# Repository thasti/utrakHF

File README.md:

# utrakHF

A pico-balloon tracker implementing WSPR transmission on ham radio frequencies.

## Usage

For launch of this payload, a valid amateur radio callsign and permission for use on an airborne vehicle is required. To configure the software for flight, edit the defines for primary and secondary callsigns in tlm.h. The assignment of secondary callsigns is handled on KD2EAT's web site: http://hojoham.blogspot.com/2016/10/known-flight-ids.html

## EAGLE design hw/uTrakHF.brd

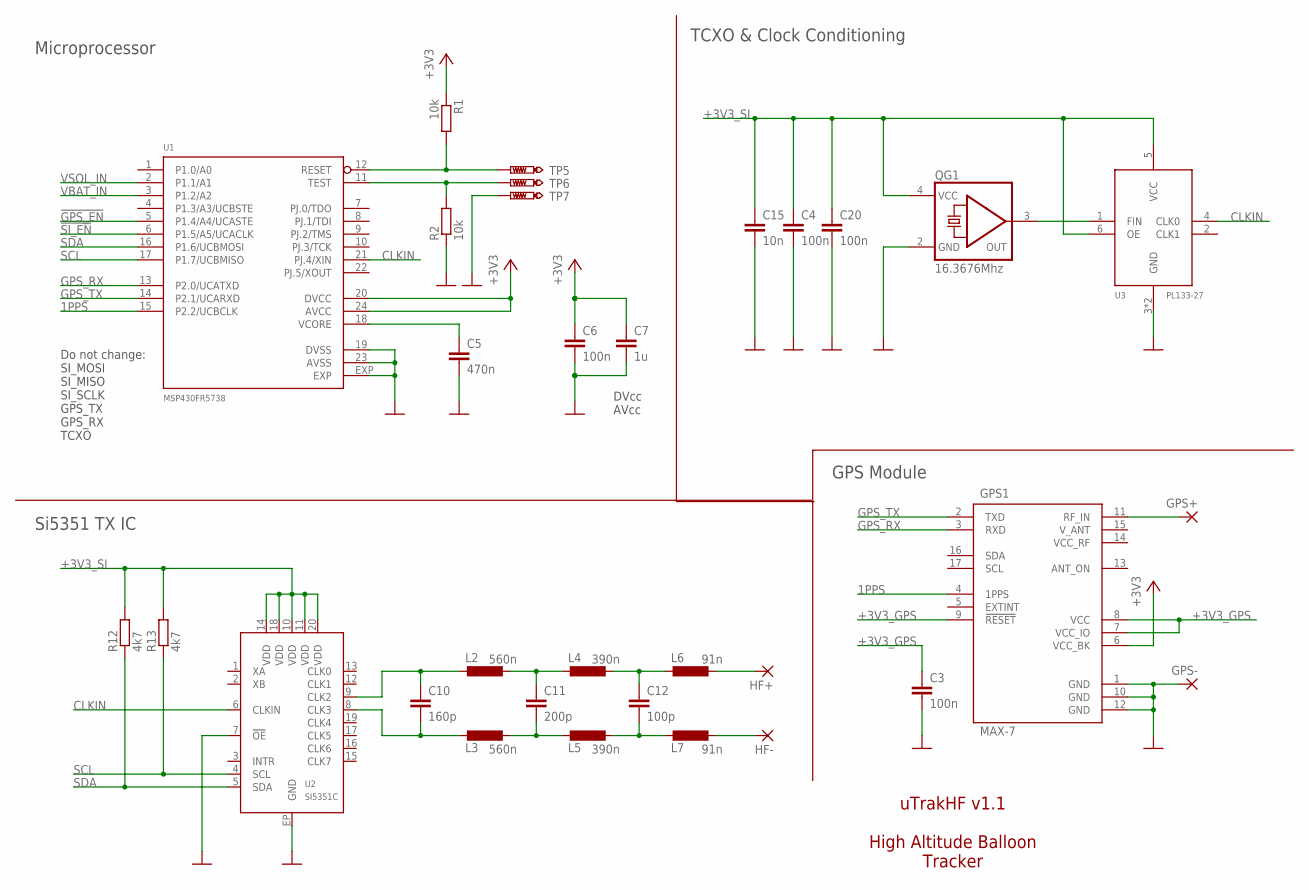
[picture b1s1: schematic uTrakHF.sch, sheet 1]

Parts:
C3, C4, C6, C20: 100n; C0402; PARTNO 81-GRM155R71C104KA88
C5: 470n; C0603; PARTNO 81-GCM188R71C474KA5D
C7: 1u; C0603; PARTNO 81-GRM39R105K10
C10: 160p; C0402; PARTNO 81-GRM1555C1H161JA01
C11: 200p; C0402; PARTNO 81-GRM1555C1H201JA1D
C12: 100p; C0402; PARTNO 81-GRM1555C1H101JA1D
C15: 10n; C0402; PARTNO 81-GRM155R71H103MA8D
GPS1: MAX-7; UBLOX-7
GPS+: SMD2; SMD1,27-2,54
GPS-: SMD2; SMD1,27-2,54
HF+: SMD2; SMD1,27-2,54
HF-: SMD2; SMD1,27-2,54
L2, L3: 560n; C0603; PARTNO 810-MLJ1608WR56JT000
L4, L5: 390n; C0603; PARTNO 810-MLJ1608WR39JT000
L6, L7: 91n; C0603; PARTNO 81-LQW18AN91NG00D
QG1: 16.3676Mhz; CTS406
R1, R2: 10k; R0402; PARTNO 603-RC0402FR-0710KL
R12, R13: 4k7; R0402; PARTNO 603-RC0402FR-074K7L
TP5, TP6, TP7: PTR1TP10SQ; TP10SQ
U1: MSP430FR5738; QFN24-4X4; PARTNO 595-SP430FR5738IRGER
U2: SI5351C; QFN20-4X4; PARTNO 634-SI5351C-B-GM
U3: PL133-27; DFN6-2X3; PARTNO 998-PL133-27GC-R

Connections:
1PPS: GPS1.4 (1PPS), U1.15 (P2.2/UCBCLK)
!GPS_EN: U1.5 (P1.4/A4/UCASTE); also elsewhere on the board
!SI_EN: U1.6 (P1.5/A5/UCACLK); also elsewhere on the board
+3V3: C6.1, C7.1, GPS1.6 (VCC_BK), R1.1, U1.20 (DVCC), U1.24 (AVCC); also elsewhere on the board
+3V3_GPS: C3.1, GPS1.7 (VCC_IO), GPS1.8 (VCC), GPS1.9 (!RESET); also elsewhere on the board
+3V3_SI: C4.1, C15.1, C20.1, QG1.4 (VCC), R12.2, R13.2, U2.10 (VDD), U2.11 (VDD), U2.14 (VDD), U2.18 (VDD), U2.20 (VDD), U3.5 (VCC), U3.6 (OE); also elsewhere on the board
C33: C10.1, L2.1, U2.9 (CLK2)
CLKIN: U1.21 (PJ.4/XIN), U2.6 (CLKIN), U3.4 (CLK0)
GND: C3.2, C4.2, C5.2, C6.2, C7.2, C15.2, C20.2, GPS1.1 (GND), GPS1.10 (GND), GPS1.12 (GND), GPS-.1, QG1.2 (GND), R2.1, TP7.TP, U1.19 (DVSS), U1.23 (AVSS), U1.EXP, U2.7 (!OE), U2.EP (GND), U3.3 (GND), U3.EXP (GND); also elsewhere on the board
GPS+: GPS1.11 (RF_IN), GPS+.1
GPS_RX: GPS1.3 (RXD), U1.13 (P2.0/UCATXD)
GPS_TX: GPS1.2 (TXD), U1.14 (P2.1/UCARXD)
HF+: HF+.1, L6.2
HF-: HF-.1, L7.2
unnamed: C5.1, U1.18 (VCORE)
unnamed: C11.1, L2.2, L4.1
unnamed: C12.1, L4.2, L6.1
unnamed: C10.2, L3.1, U2.8 (CLK3)
unnamed: C11.2, L3.2, L5.1
unnamed: C12.2, L5.2, L7.1
RST: R1.2, TP5.TP, U1.12 (RESET)
SCL: R13.1, U1.17 (P1.7/UCBMISO), U2.4 (SCL)
SDA: R12.1, U1.16 (P1.6/UCBMOSI), U2.5 (SDA)
TCXO: QG1.3 (OUT), U3.1 (FIN)
TST: R2.2, TP6.TP, U1.11 (TEST)
VBAT_IN: U1.3 (P1.2/A2); also elsewhere on the board
VSOL_IN: U1.2 (P1.1/A1); also elsewhere on the board

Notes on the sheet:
GPS Module
Microprocessor
DVcc AVcc
Do not change: SI_MOSI SI_MISO SI_SCLK GPS_TX GPS_RX TCXO
Si5351 TX IC
TCXO & Clock Conditioning
uTrakHF v1.1 High Altitude Balloon Tracker

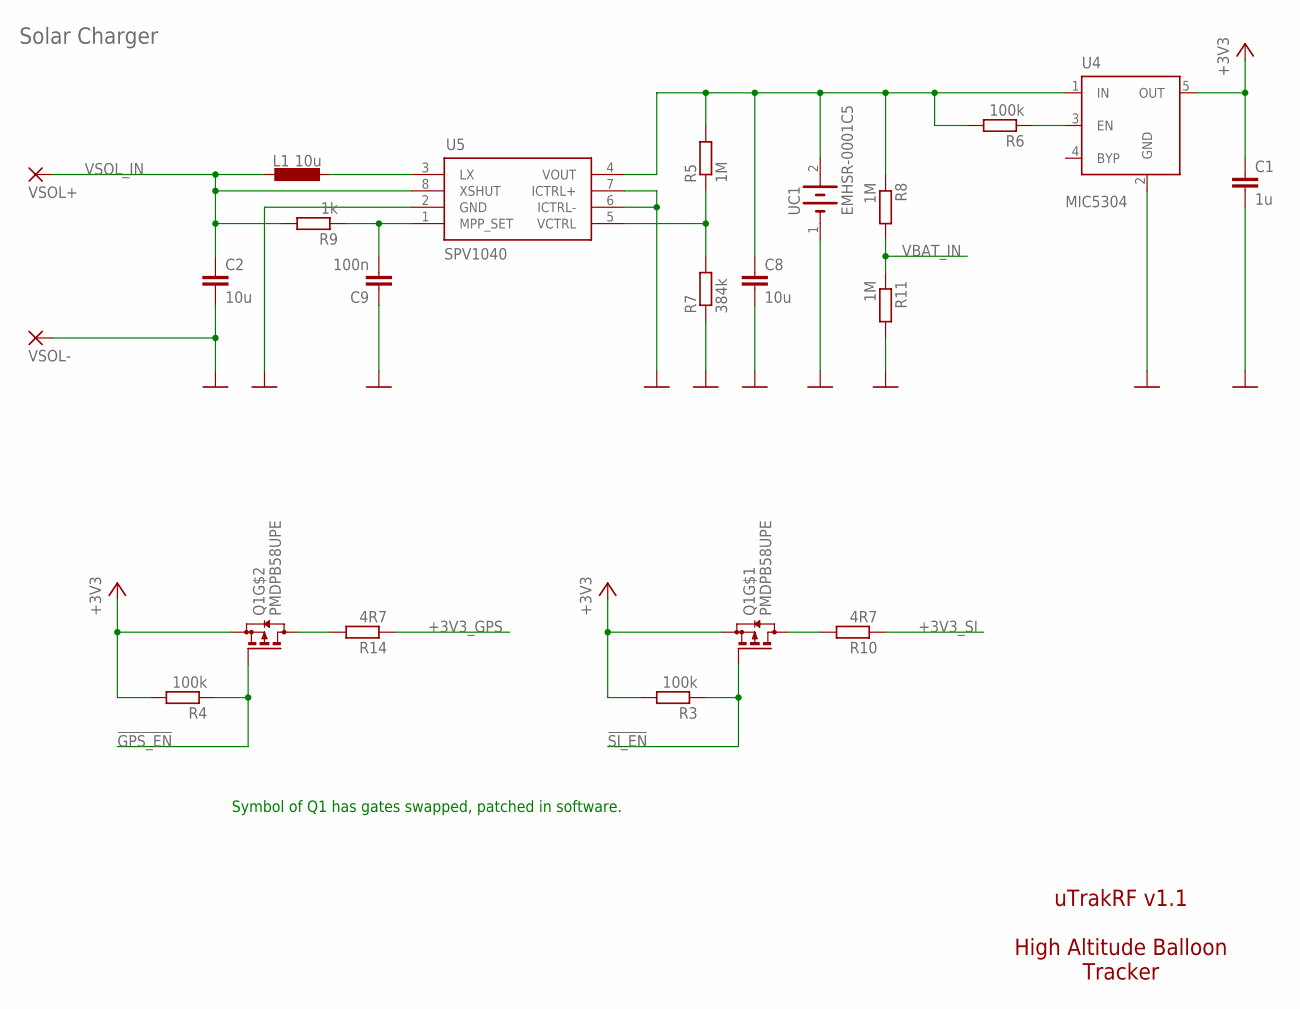
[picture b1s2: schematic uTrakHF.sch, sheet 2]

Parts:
C1: 1u; C0603
C2, C8: 10u; C0603
C9: 100n; C0402
L1: 10u; LPS4018; PARTNO 994-LPS4018-223MRB
Q1: PMDPB58UPE; SOT1118; PARTNO 771-PMDPB58UPE,115
R3, R4: 100k; R0402; PARTNO 603-RC0402FR-07100KL
R5: 1M; R0402
R6: 100k; R0402
R7: 384k; R0402
R8, R11: 1M; R0402; PARTNO 603-RC0402FR-071ML
R9: 1k; R0402
R10, R14: 4R7; R0402; PARTNO 603-RC0402FR-07100KL
U4: MIC5304; SOT23-5
U5: SPV1040; TSSOP8
UC1: EMHSR-0001C5; EMHSR-0001C5-005R0; PARTNO 581-SCMR22C155MRBA0
VSOL+: SMD2; SMD1,27-2,54
VSOL-: SMD2; SMD1,27-2,54

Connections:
!GPS_EN: Q1.5 (G), R4.1; also elsewhere on the board
!SI_EN: Q1.2 (G), R3.1; also elsewhere on the board
+3V3: C1.1, Q1.1 (S), Q1.4 (S), R3.2, R4.2, U4.5 (OUT); also elsewhere on the board
+3V3_GPS: R14.1; also elsewhere on the board
+3V3_SI: R10.1; also elsewhere on the board
GND: C1.2, C2.2, C8.2, C9.1, R7.1, R11.2, U4.2 (GND), U5.2 (GND), U5.6 (ICTRL-), U5.7 (ICTRL+), UC1.1 (-), VSOL-.1; also elsewhere on the board
unnamed: Q1.3 (D), Q1.8 (D), R10.2
unnamed: Q1.6 (D), Q1.7 (D), R14.2
unnamed: R6.1, U4.3 (EN)
unnamed: L1.1, U5.3 (LX)
unnamed: C9.2, R9.1, U5.1 (MPP_SET)
unnamed: R5.1, R7.2, U5.5 (VCTRL)
VBAT: C8.1, R5.2, R6.2, R8.1, U4.1 (IN), U5.4 (VOUT), UC1.2 (+)
VBAT_IN: R8.2, R11.1; also elsewhere on the board
VSOL_IN: C2.1, L1.2, R9.2, U5.8 (XSHUT), VSOL+.1; also elsewhere on the board

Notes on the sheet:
Solar Charger
uTrakRF v1.1 High Altitude Balloon Tracker
Symbol of Q1 has gates swapped, patched in software.

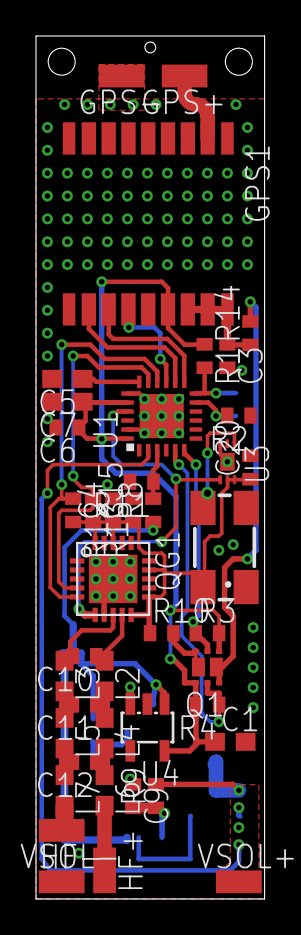
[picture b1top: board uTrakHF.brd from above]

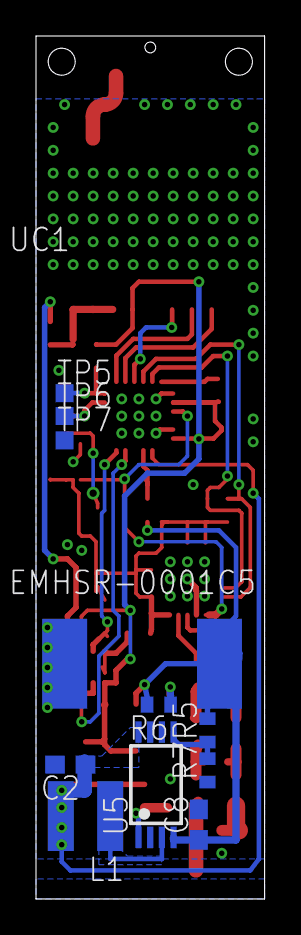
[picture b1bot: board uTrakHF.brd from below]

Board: 2 copper layers, 12.7 x 47.9 mm, 53 parts (11 on the bottom side), 34 nets.

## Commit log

2017-07-12 initial API specification, no functionality
2017-07-13 add low-level driver functionality
2017-07-13 change repo name
2017-07-13 implement Si5351 WSPR-optimized(tm) driver
2017-07-13 add GPS driver
2017-07-14 implement state machine & sequencing functionality
2017-07-14 add telemetry encoding, first parts of WSPR encoding
2017-07-14 finish WSPR implementation, add test software
2017-07-14 add battery / solar voltage limits for each operating state
2017-07-14 fix copy/paste bug
2017-07-14 improve readability of WSPR TX start condition
2017-07-15 fix I2C write transfer
2017-07-15 add gitignore
2017-07-17 factor out delays into hw.c, review ADC settings
2017-07-17 change WSPR telemetry format
2017-07-18 add EAGLE design files
2017-07-18 fix WSPR telemetry implementation bugs
2017-07-18 add telemetry encoding test program
2017-07-18 transmit primary WSPR packet only every 10 minutes
2017-08-07 fix ADC measurement
2017-08-08 fix small bugs
2017-08-13 apply consistency fixes, fix solar/battery mixup
2017-08-18 software fixes for I2C / Si5351
2017-08-19 fix WSPR encoding bug
2017-08-19 fix hw.c indentation, make ACLK = DCO/16
2017-08-22 fix Si5351 clock generation
2017-08-22 use DCO/2 for UART
2017-08-22 don't wake up GPS, no power-save mode is used
2017-08-22 fix gps.c indentation
2017-08-23 ignore ACKs for settings for now..
2017-08-23 adapt WSPR start time
2017-08-24 add new voltage limits
2017-08-24 fix missed ACLK dependencies for ADC
2018-04-18 fix init bug, change secondary call for 0x11
2018-04-27 add hardware errata
2018-05-02 add schematic PDF
2019-08-22 bump callsign+indicator for 0x14
2019-08-22 frequency update for 0x14
2019-09-04 update hardware design documentation
2019-09-04 configuration documentation
2019-09-21 change callsign for miamihab missions
2019-09-22 fix primary callsign for miamihab
2019-09-22 revert back to first second transmission to decrease DT
2019-09-22 add indicator for callsign formatting
